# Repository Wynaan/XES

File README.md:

# XES

This repository details my end of degree project in Electronics Technology at Cegep Saint-Jean-sur-Richelieu.

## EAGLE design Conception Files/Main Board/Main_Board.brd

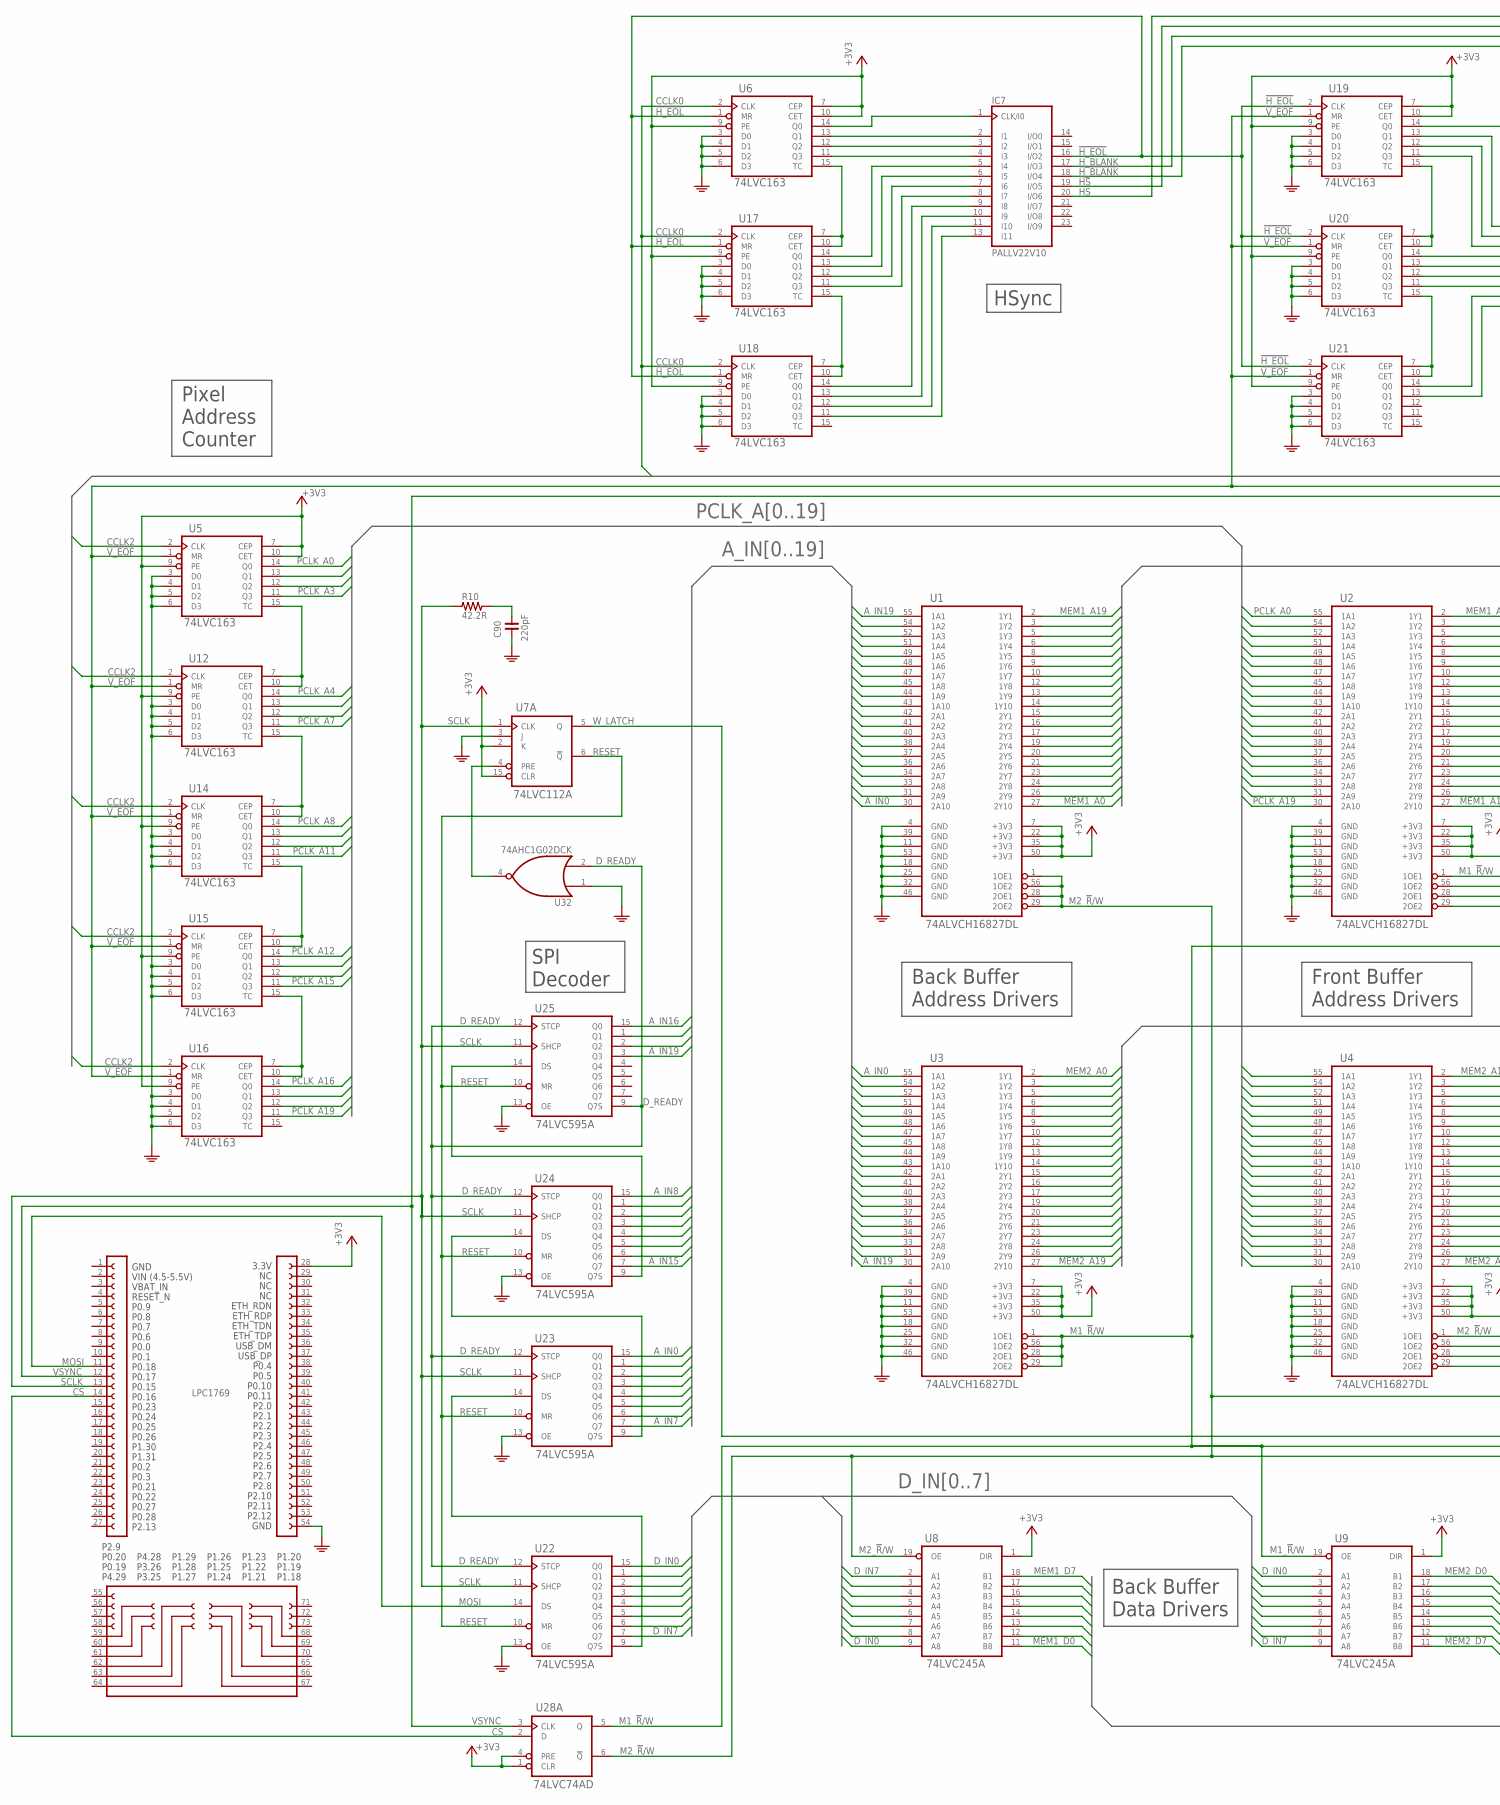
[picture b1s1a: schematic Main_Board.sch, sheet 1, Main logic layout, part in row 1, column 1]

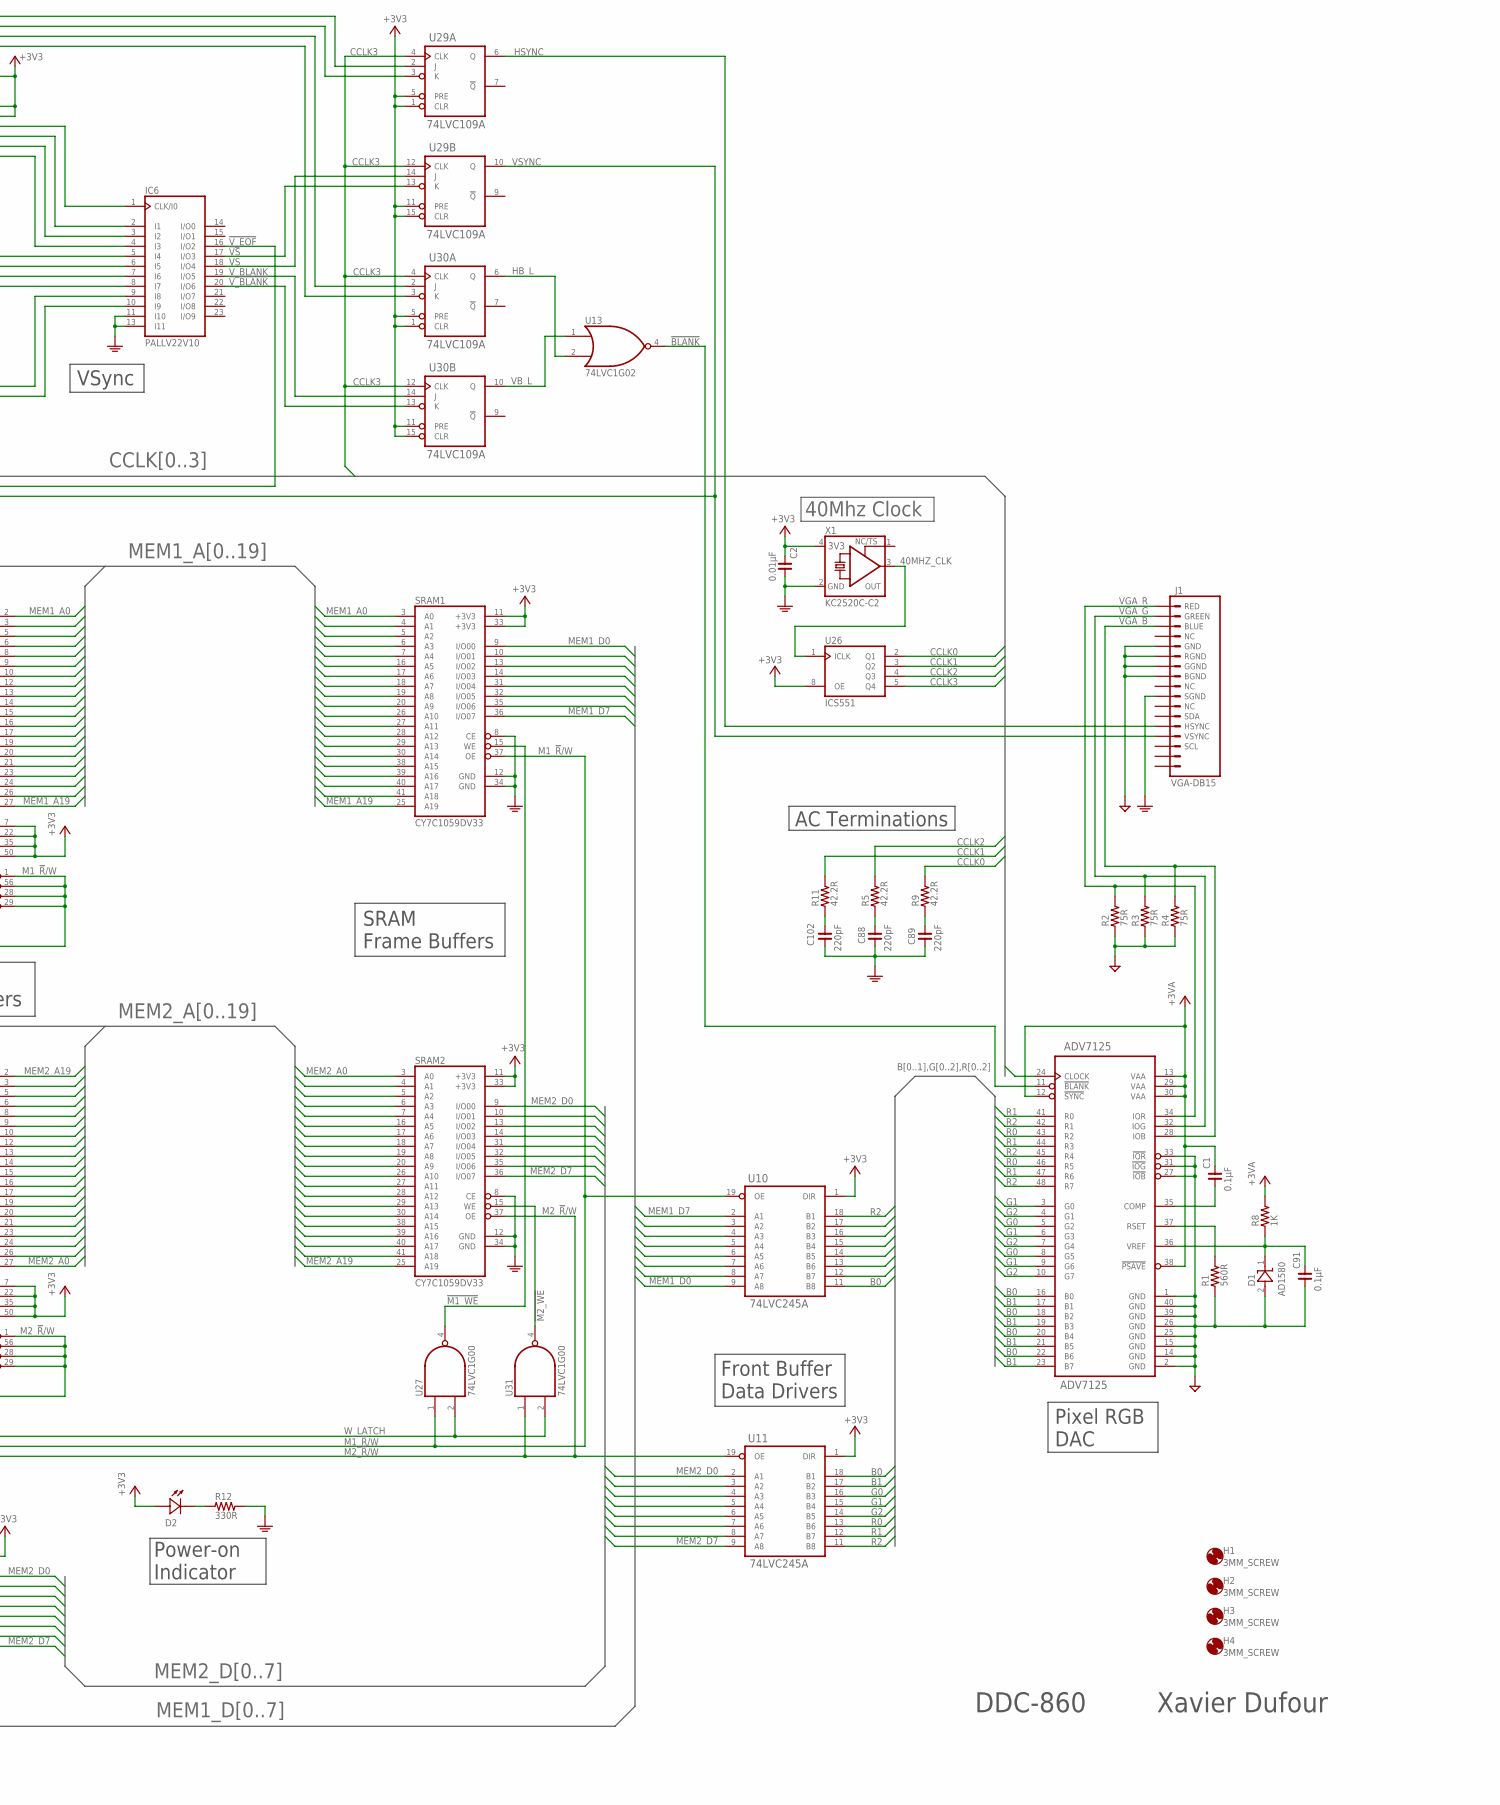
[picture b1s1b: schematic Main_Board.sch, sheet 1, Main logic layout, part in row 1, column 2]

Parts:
ADV7125: ADV7125; LQFP48(SOT313)
C1, C91: 0.1µF; C0603
C2: 0.01µF; C0603
C88, C89, C90, C102: 220pF; C0603
D1: AD1580; TO236-3(SOT23)
D2: DEL-1206; DEL1206
H1, H2, H3, H4: 3MM_SCREW; 3MM_HOLE
IC6, IC7: PALLV22V10; DIP24
J1: VGA-DB15; DB15-VGA-90DEG
LPC1769: LPCXPRESSO_LPC1769
R1: 560R; R0603
R2, R3, R4: 75R; R0603
R5, R9, R10, R11: 42.2R; R0603
R8: 1K; R0603
R12: 330R; R1206
SRAM1, SRAM2: CY7C1059DV33; TSOPII-44
U1, U2, U3, U4: 74ALVCH16827DL; SSOP56(SOT371)
U5, U6, U12, U14, U15, U16, U17, U18, U19, U20, U21: 74LVC163; SO16D(SOT109)
U7: 74LVC112A; SO16D(SOT109)
U8, U9, U10, U11: 74LVC245A; SO20DW(SOT163)
U13: 74LVC1G02; SC70-5(SOT353)
U22, U23, U24, U25: 74LVC595A; SO16D(SOT109)
U26: ICS551; SO08(SOT96)
U27, U31: 74LVC1G00; SC70-5(SOT353)
U28: 74LVC74AD; SO14(SOT108)
U29, U30: 74LVC109A; SO16D(SOT109)
U32: 74AHC1G02DCK; SC70-5(SOT353)
X1: KC2520C-C2; OSCXO2.5X2.0

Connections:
40MHZ_CLK: U26.1 (ICLK), X1.3 (OUT)
!BLANK: ADV7125.11 (!BLANK), U13.4 (Y)
!HS: IC7.19 (I/O5), U29.3 (K)
!H_BLANK: IC7.18 (I/O4), U30.3 (K)
!H_EOL: IC7.16 (I/O2), U6.1 (MR), U17.1 (MR), U18.1 (MR), U19.2 (CLK), U20.2 (CLK), U21.2 (CLK)
!M1_WE: SRAM1.15 (WE), U27.4 (Y)
!M2_WE: SRAM2.15 (WE), U31.4 (Y)
!VS: IC6.17 (I/O3), U29.13 (K)
!V_BLANK: IC6.20 (I/O6), U30.13 (K)
!V_EOF: IC6.16 (I/O2), U5.1 (MR), U12.1 (MR), U14.1 (MR), U15.1 (MR), U16.1 (MR), U19.1 (MR), U20.1 (MR), U21.1 (MR)
+3V3: C2.2, D2.A, IC6.24 (+3V3), IC7.24 (+3V3), LPC1769.28, SRAM1.11 (+3V3), SRAM1.33 (+3V3), SRAM2.11 (+3V3), SRAM2.33 (+3V3), U1.7 (+3V3), U1.22 (+3V3), U1.35 (+3V3), U1.50 (+3V3), U2.7 (+3V3), U2.22 (+3V3), U2.35 (+3V3), U2.50 (+3V3), U3.7 (+3V3), U3.22 (+3V3), U3.35 (+3V3), U3.50 (+3V3), U4.7 (+3V3), U4.22 (+3V3), U4.35 (+3V3), U4.50 (+3V3), U5.7 (CEP), U5.9 (PE), U5.10 (CET), U5.16 (+3V3), U6.7 (CEP), U6.9 (PE), U6.10 (CET), U6.16 (+3V3), U7.2 (K), U7.15 (CLR), U7.16 (+3V3), U8.1 (DIR), U8.20 (+3V3), U9.1 (DIR), U9.20 (+3V3), U10.1 (DIR), U10.20 (+3V3), U11.1 (DIR), U11.20 (+3V3), U12.9 (PE), U12.16 (+3V3), U13.5 (+3V3), U14.9 (PE), U14.16 (+3V3), U15.9 (PE), U15.16 (+3V3), U16.9 (PE), U16.16 (+3V3), U17.9 (PE), U17.16 (+3V3), U18.9 (PE), U18.16 (+3V3), U19.7 (CEP), U19.9 (PE), U19.10 (CET), U19.16 (+3V3), U20.9 (PE), U20.16 (+3V3), U21.9 (PE), U21.16 (+3V3), U22.16 (+3V3), U23.16 (+3V3), U24.16 (+3V3), U25.16 (+3V3), U26.7 (+3V3), U26.8 (OE), U27.5 (+3V3), U28.1 (CLR), U28.4 (PRE), U28.14 (+3V3), U29.1 (CLR), U29.5 (PRE), U29.11 (PRE), U29.15 (CLR), U29.16 (+3V3), U30.1 (CLR), U30.5 (PRE), U30.11 (PRE), U30.15 (CLR), U30.16 (+3V3), U31.5 (+3V3), U32.5 (+3V3), X1.4 (+3V3); also elsewhere on the board
+3VA: ADV7125.12 (!SYNC), ADV7125.13 (VAA), ADV7125.29 (VAA), ADV7125.30 (VAA), ADV7125.38 (!PSAVE), C1.2, R8.2; also elsewhere on the board
AGND: ADV7125.1 (GND), ADV7125.2 (GND), ADV7125.14 (GND), ADV7125.15 (GND), ADV7125.25 (GND), ADV7125.26 (GND), ADV7125.27 (!IOB), ADV7125.31 (!IOG), ADV7125.33 (!IOR), ADV7125.39 (GND), ADV7125.40 (GND), C91.1, D1.2 (V-), J1.5 (GND), J1.6 (RGND), J1.7 (GGND), J1.8 (BGND), R1.1, R2.1, R3.1, R4.1; also elsewhere on the board
A_IN0: U1.30 (2A10), U3.55 (1A1), U23.15 (Q0)
A_IN1: U1.31 (2A9), U3.54 (1A2), U23.1 (Q1)
A_IN2: U1.33 (2A8), U3.52 (1A3), U23.2 (Q2)
A_IN3: U1.34 (2A7), U3.51 (1A4), U23.3 (Q3)
A_IN4: U1.36 (2A6), U3.49 (1A5), U23.4 (Q4)
A_IN5: U1.37 (2A5), U3.48 (1A6), U23.5 (Q5)
A_IN6: U1.38 (2A4), U3.47 (1A7), U23.6 (Q6)
A_IN7: U1.40 (2A3), U3.45 (1A8), U23.7 (Q7)
A_IN8: U1.41 (2A2), U3.44 (1A9), U24.15 (Q0)
A_IN9: U1.42 (2A1), U3.43 (1A10), U24.1 (Q1)
A_IN10: U1.43 (1A10), U3.42 (2A1), U24.2 (Q2)
A_IN11: U1.44 (1A9), U3.41 (2A2), U24.3 (Q3)
A_IN12: U1.45 (1A8), U3.40 (2A3), U24.4 (Q4)
A_IN13: U1.47 (1A7), U3.38 (2A4), U24.5 (Q5)
A_IN14: U1.48 (1A6), U3.37 (2A5), U24.6 (Q6)
A_IN15: U1.49 (1A5), U3.36 (2A6), U24.7 (Q7)
A_IN16: U1.51 (1A4), U3.34 (2A7), U25.15 (Q0)
A_IN17: U1.52 (1A3), U3.33 (2A8), U25.1 (Q1)
A_IN18: U1.54 (1A2), U3.31 (2A9), U25.2 (Q2)
A_IN19: U1.55 (1A1), U3.30 (2A10), U25.3 (Q3)
B0: ADV7125.16 (B0), ADV7125.18 (B2), ADV7125.20 (B4), ADV7125.22 (B6), U10.11 (B8), U11.18 (B1)
B1: ADV7125.17 (B1), ADV7125.19 (B3), ADV7125.21 (B5), ADV7125.23 (B7), U10.12 (B7), U11.17 (B2)
CCLK0: R9.2, U6.2 (CLK), U17.2 (CLK), U18.2 (CLK), U26.2 (Q1)
CCLK1: ADV7125.24 (CLOCK), R11.2, U26.3 (Q2)
CCLK2: R5.2, U5.2 (CLK), U12.2 (CLK), U14.2 (CLK), U15.2 (CLK), U16.2 (CLK), U26.4 (Q3)
CCLK3: U26.5 (Q4), U29.4 (CLK), U29.12 (CLK), U30.4 (CLK), U30.12 (CLK)
COMP: ADV7125.35 (COMP), C1.1
CS: LPC1769.14, U28.2 (D)
D_IN0: U8.9 (A8), U9.2 (A1), U22.15 (Q0)
D_IN1: U8.8 (A7), U9.3 (A2), U22.1 (Q1)
D_IN2: U8.7 (A6), U9.4 (A3), U22.2 (Q2)
D_IN3: U8.6 (A5), U9.5 (A4), U22.3 (Q3)
D_IN4: U8.5 (A4), U9.6 (A5), U22.4 (Q4)
D_IN5: U8.4 (A3), U9.7 (A6), U22.5 (Q5)
D_IN6: U8.3 (A2), U9.8 (A7), U22.6 (Q6)
D_IN7: U8.2 (A1), U9.9 (A8), U22.7 (Q7)
D_READY: U22.12 (STCP), U23.12 (STCP), U24.12 (STCP), U25.9 (Q7S), U25.12 (STCP), U32.2 (B)
G0: ADV7125.5 (G2), ADV7125.8 (G5), U10.13 (B6), U11.16 (B3)
G1: ADV7125.3 (G0), ADV7125.6 (G3), ADV7125.9 (G6), U10.14 (B5), U11.15 (B4)
G2: ADV7125.4 (G1), ADV7125.7 (G4), ADV7125.10 (G7), U10.15 (B4), U11.14 (B5)
GND: C2.1, C88.1, C89.1, C90.1, C102.1, IC6.11 (I10), IC6.12 (GND), IC6.13 (I11), IC7.12 (GND), J1.10 (SGND), LPC1769.54, R12.2, SRAM1.8 (CE), SRAM1.12 (GND), SRAM1.34 (GND), SRAM2.8 (CE), SRAM2.12 (GND), SRAM2.34 (GND), U1.4 (GND), U1.11 (GND), U1.18 (GND), U1.25 (GND), U1.32 (GND), U1.39 (GND), U1.46 (GND), U1.53 (GND), U2.4 (GND), U2.11 (GND), U2.18 (GND), U2.25 (GND), U2.32 (GND), U2.39 (GND), U2.46 (GND), U2.53 (GND), U3.4 (GND), U3.11 (GND), U3.18 (GND), U3.25 (GND), U3.32 (GND), U3.39 (GND), U3.46 (GND), U3.53 (GND), U4.4 (GND), U4.11 (GND), U4.18 (GND), U4.25 (GND), U4.32 (GND), U4.39 (GND), U4.46 (GND), U4.53 (GND), U5.3 (D0), U5.4 (D1), U5.5 (D2), U5.6 (D3), U5.8 (GND), U6.3 (D0), U6.4 (D1), U6.5 (D2), U6.6 (D3), U6.8 (GND), U7.3 (J), U7.8 (GND), U8.10 (GND), U9.10 (GND), U10.10 (GND), U11.10 (GND), U12.3 (D0), U12.4 (D1), U12.5 (D2), U12.6 (D3), U12.8 (GND), U13.3 (GND), U14.3 (D0), U14.4 (D1), U14.5 (D2), U14.6 (D3), U14.8 (GND), U15.3 (D0), U15.4 (D1), U15.5 (D2), U15.6 (D3), U15.8 (GND), U16.3 (D0), U16.4 (D1), U16.5 (D2), U16.6 (D3), U16.8 (GND), U17.3 (D0), U17.4 (D1), U17.5 (D2), U17.6 (D3), U17.8 (GND), U18.3 (D0), U18.4 (D1), U18.5 (D2), U18.6 (D3), U18.8 (GND), U19.3 (D0), U19.4 (D1), U19.5 (D2), U19.6 (D3), U19.8 (GND), U20.3 (D0), U20.4 (D1), U20.5 (D2), U20.6 (D3), U20.8 (GND), U21.3 (D0), U21.4 (D1), U21.5 (D2), U21.6 (D3), U21.8 (GND), U22.8 (GND), U22.13 (OE), U23.8 (GND), U23.13 (OE), U24.8 (GND), U24.13 (OE), U25.8 (GND), U25.13 (OE), U26.6 (GND), U27.3 (GND), U28.7 (GND), U29.8 (GND), U30.8 (GND), U31.3 (GND), U32.1 (A), U32.3 (GND), X1.2 (GND); also elsewhere on the board
HB_L: U13.2 (B), U30.6 (Q)
HS: IC7.20 (I/O6), U29.2 (J)
HSYNC: J1.13 (HSYNC), U29.6 (Q)
H_BLANK: IC7.17 (I/O3), U30.2 (J)
H_Q0: IC7.1 (CLK/I0), U6.14 (Q0)
H_Q1: IC7.2 (I1), U6.13 (Q1)
H_Q2: IC7.3 (I2), U6.12 (Q2)
H_Q3: IC7.4 (I3), U6.11 (Q3)
H_Q4: IC7.5 (I4), U17.14 (Q0)
H_Q5: IC7.6 (I5), U17.13 (Q1)
H_Q6: IC7.7 (I6), U17.12 (Q2)
H_Q7: IC7.8 (I7), U17.11 (Q3)
H_Q8: IC7.9 (I8), U18.14 (Q0)
H_Q9: IC7.10 (I9), U18.13 (Q1)
H_Q10: IC7.11 (I10), U18.12 (Q2)
H_Q11: IC7.13 (I11), U18.11 (Q3)
M1_!R!/W: SRAM1.37 (OE), U2.1 (1OE1), U2.28 (2OE1), U2.29 (2OE2), U2.56 (1OE2), U3.1 (1OE1), U3.28 (2OE1), U3.29 (2OE2), U3.56 (1OE2), U9.19 (OE), U10.19 (OE), U27.1 (B), U28.5 (Q)
M2_!R!/W: SRAM2.37 (OE), U1.1 (1OE1), U1.28 (2OE1), U1.29 (2OE2), U1.56 (1OE2), U4.1 (1OE1), U4.28 (2OE1), U4.29 (2OE2), U4.56 (1OE2), U8.19 (OE), U11.19 (OE), U28.6 (!Q), U31.1 (B)
MEM1_A0: SRAM1.3 (A0), U1.27 (2Y10), U2.2 (1Y1)
MEM1_A1: SRAM1.4 (A1), U1.26 (2Y9), U2.3 (1Y2)
MEM1_A2: SRAM1.5 (A2), U1.24 (2Y8), U2.5 (1Y3)
MEM1_A3: SRAM1.6 (A3), U1.23 (2Y7), U2.6 (1Y4)
MEM1_A4: SRAM1.7 (A4), U1.21 (2Y6), U2.8 (1Y5)
MEM1_A5: SRAM1.16 (A5), U1.20 (2Y5), U2.9 (1Y6)
MEM1_A6: SRAM1.17 (A6), U1.19 (2Y4), U2.10 (1Y7)
MEM1_A7: SRAM1.18 (A7), U1.17 (2Y3), U2.12 (1Y8)
MEM1_A8: SRAM1.19 (A8), U1.16 (2Y2), U2.13 (1Y9)
MEM1_A9: SRAM1.20 (A9), U1.15 (2Y1), U2.14 (1Y10)
MEM1_A10: SRAM1.26 (A10), U1.14 (1Y10), U2.15 (2Y1)
MEM1_A11: SRAM1.27 (A11), U1.13 (1Y9), U2.16 (2Y2)
MEM1_A12: SRAM1.28 (A12), U1.12 (1Y8), U2.17 (2Y3)
MEM1_A13: SRAM1.29 (A13), U1.10 (1Y7), U2.19 (2Y4)
MEM1_A14: SRAM1.30 (A14), U1.9 (1Y6), U2.20 (2Y5)
MEM1_A15: SRAM1.38 (A15), U1.8 (1Y5), U2.21 (2Y6)
MEM1_A16: SRAM1.39 (A16), U1.6 (1Y4), U2.23 (2Y7)
MEM1_A17: SRAM1.40 (A17), U1.5 (1Y3), U2.24 (2Y8)
MEM1_A18: SRAM1.41 (A18), U1.3 (1Y2), U2.26 (2Y9)
MEM1_A19: SRAM1.25 (A19), U1.2 (1Y1), U2.27 (2Y10)
MEM1_D0: SRAM1.9 (I/O00), U8.11 (B8), U10.9 (A8)
MEM1_D1: SRAM1.10 (I/O01), U8.12 (B7), U10.8 (A7)
MEM1_D2: SRAM1.13 (I/O02), U8.13 (B6), U10.7 (A6)
MEM1_D3: SRAM1.14 (I/O03), U8.14 (B5), U10.6 (A5)
MEM1_D4: SRAM1.31 (I/O04), U8.15 (B4), U10.5 (A4)
MEM1_D5: SRAM1.32 (I/O05), U8.16 (B3), U10.4 (A3)
MEM1_D6: SRAM1.35 (I/O06), U8.17 (B2), U10.3 (A2)
MEM1_D7: SRAM1.36 (I/O07), U8.18 (B1), U10.2 (A1)
MEM2_A0: SRAM2.3 (A0), U3.2 (1Y1), U4.27 (2Y10)
MEM2_A1: SRAM2.4 (A1), U3.3 (1Y2), U4.26 (2Y9)
MEM2_A2: SRAM2.5 (A2), U3.5 (1Y3), U4.24 (2Y8)
MEM2_A3: SRAM2.6 (A3), U3.6 (1Y4), U4.23 (2Y7)
MEM2_A4: SRAM2.7 (A4), U3.8 (1Y5), U4.21 (2Y6)
MEM2_A5: SRAM2.16 (A5), U3.9 (1Y6), U4.20 (2Y5)
MEM2_A6: SRAM2.17 (A6), U3.10 (1Y7), U4.19 (2Y4)
MEM2_A7: SRAM2.18 (A7), U3.12 (1Y8), U4.17 (2Y3)
MEM2_A8: SRAM2.19 (A8), U3.13 (1Y9), U4.16 (2Y2)
MEM2_A9: SRAM2.20 (A9), U3.14 (1Y10), U4.15 (2Y1)
MEM2_A10: SRAM2.26 (A10), U3.15 (2Y1), U4.14 (1Y10)
MEM2_A11: SRAM2.27 (A11), U3.16 (2Y2), U4.13 (1Y9)
MEM2_A12: SRAM2.28 (A12), U3.17 (2Y3), U4.12 (1Y8)
MEM2_A13: SRAM2.29 (A13), U3.19 (2Y4), U4.10 (1Y7)
MEM2_A14: SRAM2.30 (A14), U3.20 (2Y5), U4.9 (1Y6)
MEM2_A15: SRAM2.38 (A15), U3.21 (2Y6), U4.8 (1Y5)
MEM2_A16: SRAM2.39 (A16), U3.23 (2Y7), U4.6 (1Y4)
MEM2_A17: SRAM2.40 (A17), U3.24 (2Y8), U4.5 (1Y3)
MEM2_A18: SRAM2.41 (A18), U3.26 (2Y9), U4.3 (1Y2)
MEM2_A19: SRAM2.25 (A19), U3.27 (2Y10), U4.2 (1Y1)
MEM2_D0: SRAM2.9 (I/O00), U9.18 (B1), U11.2 (A1)
MEM2_D1: SRAM2.10 (I/O01), U9.17 (B2), U11.3 (A2)
MEM2_D2: SRAM2.13 (I/O02), U9.16 (B3), U11.4 (A3)
MEM2_D3: SRAM2.14 (I/O03), U9.15 (B4), U11.5 (A4)
MEM2_D4: SRAM2.31 (I/O04), U9.14 (B5), U11.6 (A5)
MEM2_D5: SRAM2.32 (I/O05), U9.13 (B6), U11.7 (A6)
MEM2_D6: SRAM2.35 (I/O06), U9.12 (B7), U11.8 (A7)
MEM2_D7: SRAM2.36 (I/O07), U9.11 (B8), U11.9 (A8)
MOSI: LPC1769.11, U22.14 (DS)
unnamed: U15.15 (TC), U16.7 (CEP), U16.10 (CET)
unnamed: C88.2, R5.1
unnamed: U22.9 (Q7S), U23.14 (DS)
unnamed: U7.4 (PRE), U32.4 (Y)
unnamed: C89.2, R9.1
unnamed: U23.9 (Q7S), U24.14 (DS)
unnamed: U24.9 (Q7S), U25.14 (DS)
unnamed: U5.15 (TC), U12.7 (CEP), U12.10 (CET)
unnamed: U12.15 (TC), U14.7 (CEP), U14.10 (CET)
unnamed: U14.15 (TC), U15.7 (CEP), U15.10 (CET)
unnamed: C90.2, R10.2
unnamed: U6.15 (TC), U17.7 (CEP), U17.10 (CET)
unnamed: U17.15 (TC), U18.7 (CEP), U18.10 (CET)
unnamed: D2.C, R12.1
unnamed: C102.2, R11.1
unnamed: U19.15 (TC), U20.7 (CEP), U20.10 (CET)
unnamed: U20.15 (TC), U21.7 (CEP), U21.10 (CET)
PCLK_A0: U2.55 (1A1), U4.30 (2A10), U5.14 (Q0)
PCLK_A1: U2.54 (1A2), U4.31 (2A9), U5.13 (Q1)
PCLK_A2: U2.52 (1A3), U4.33 (2A8), U5.12 (Q2)
PCLK_A3: U2.51 (1A4), U4.34 (2A7), U5.11 (Q3)
PCLK_A4: U2.49 (1A5), U4.36 (2A6), U12.14 (Q0)
PCLK_A5: U2.48 (1A6), U4.37 (2A5), U12.13 (Q1)
PCLK_A6: U2.47 (1A7), U4.38 (2A4), U12.12 (Q2)
PCLK_A7: U2.45 (1A8), U4.40 (2A3), U12.11 (Q3)
PCLK_A8: U2.44 (1A9), U4.41 (2A2), U14.14 (Q0)
PCLK_A9: U2.43 (1A10), U4.42 (2A1), U14.13 (Q1)
PCLK_A10: U2.42 (2A1), U4.43 (1A10), U14.12 (Q2)
PCLK_A11: U2.41 (2A2), U4.44 (1A9), U14.11 (Q3)
PCLK_A12: U2.40 (2A3), U4.45 (1A8), U15.14 (Q0)
PCLK_A13: U2.38 (2A4), U4.47 (1A7), U15.13 (Q1)
PCLK_A14: U2.37 (2A5), U4.48 (1A6), U15.12 (Q2)
PCLK_A15: U2.36 (2A6), U4.49 (1A5), U15.11 (Q3)
PCLK_A16: U2.34 (2A7), U4.51 (1A4), U16.14 (Q0)
PCLK_A17: U2.33 (2A8), U4.52 (1A3), U16.13 (Q1)
PCLK_A18: U2.31 (2A9), U4.54 (1A2), U16.12 (Q2)
PCLK_A19: U2.30 (2A10), U4.55 (1A1), U16.11 (Q3)
R0: ADV7125.43 (R2), ADV7125.46 (R5), U10.16 (B3), U11.13 (B6)
R1: ADV7125.41 (R0), ADV7125.44 (R3), ADV7125.47 (R6), U10.17 (B2), U11.12 (B7)
R2: ADV7125.42 (R1), ADV7125.45 (R4), ADV7125.48 (R7), U10.18 (B1), U11.11 (B8)
RESET: U7.6 (!Q), U22.10 (MR), U23.10 (MR), U24.10 (MR), U25.10 (MR)
RSET: ADV7125.37 (RSET), R1.2
SCLK: LPC1769.13, R10.1, U7.1 (CLK), U22.11 (SHCP), U23.11 (SHCP), U24.11 (SHCP), U25.11 (SHCP)
VB_L: U13.1 (A), U30.10 (Q)
VGA_B: ADV7125.28 (IOB), J1.3 (BLUE), R4.2
VGA_G: ADV7125.32 (IOG), J1.2 (GREEN), R3.2
VGA_R: ADV7125.34 (IOR), J1.1 (RED), R2.2
VREF: ADV7125.36 (VREF), C91.2, D1.1 (V+), R8.1
VS: IC6.18 (I/O4), U29.14 (J)
VSYNC: J1.14 (VSYNC), LPC1769.12, U28.3 (CLK), U29.10 (Q)
V_BLANK: IC6.19 (I/O5), U30.14 (J)
V_Q0: IC6.1 (CLK/I0), U19.14 (Q0)
V_Q1: IC6.2 (I1), U19.13 (Q1)
V_Q2: IC6.3 (I2), U19.12 (Q2)
V_Q3: IC6.4 (I3), U19.11 (Q3)
V_Q4: IC6.5 (I4), U20.14 (Q0)
V_Q5: IC6.6 (I5), U20.13 (Q1)
V_Q6: IC6.7 (I6), U20.12 (Q2)
V_Q7: IC6.8 (I7), U20.11 (Q3)
V_Q8: IC6.9 (I8), U21.14 (Q0)
V_Q9: IC6.10 (I9), U21.13 (Q1)
W_LATCH: U7.5 (Q), U27.2 (A), U31.2 (A)

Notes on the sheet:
SRAM Frame Buffers
Back Buffer Address Drivers
Front Buffer Address Drivers
Front Buffer Data Drivers
Back Buffer Data Drivers
Pixel Address Counter
SPI Decoder
Pixel RGB DAC
VSync
HSync
40Mhz Clock
DDC-860 Xavier Dufour
Power-on Indicator
AC Terminations

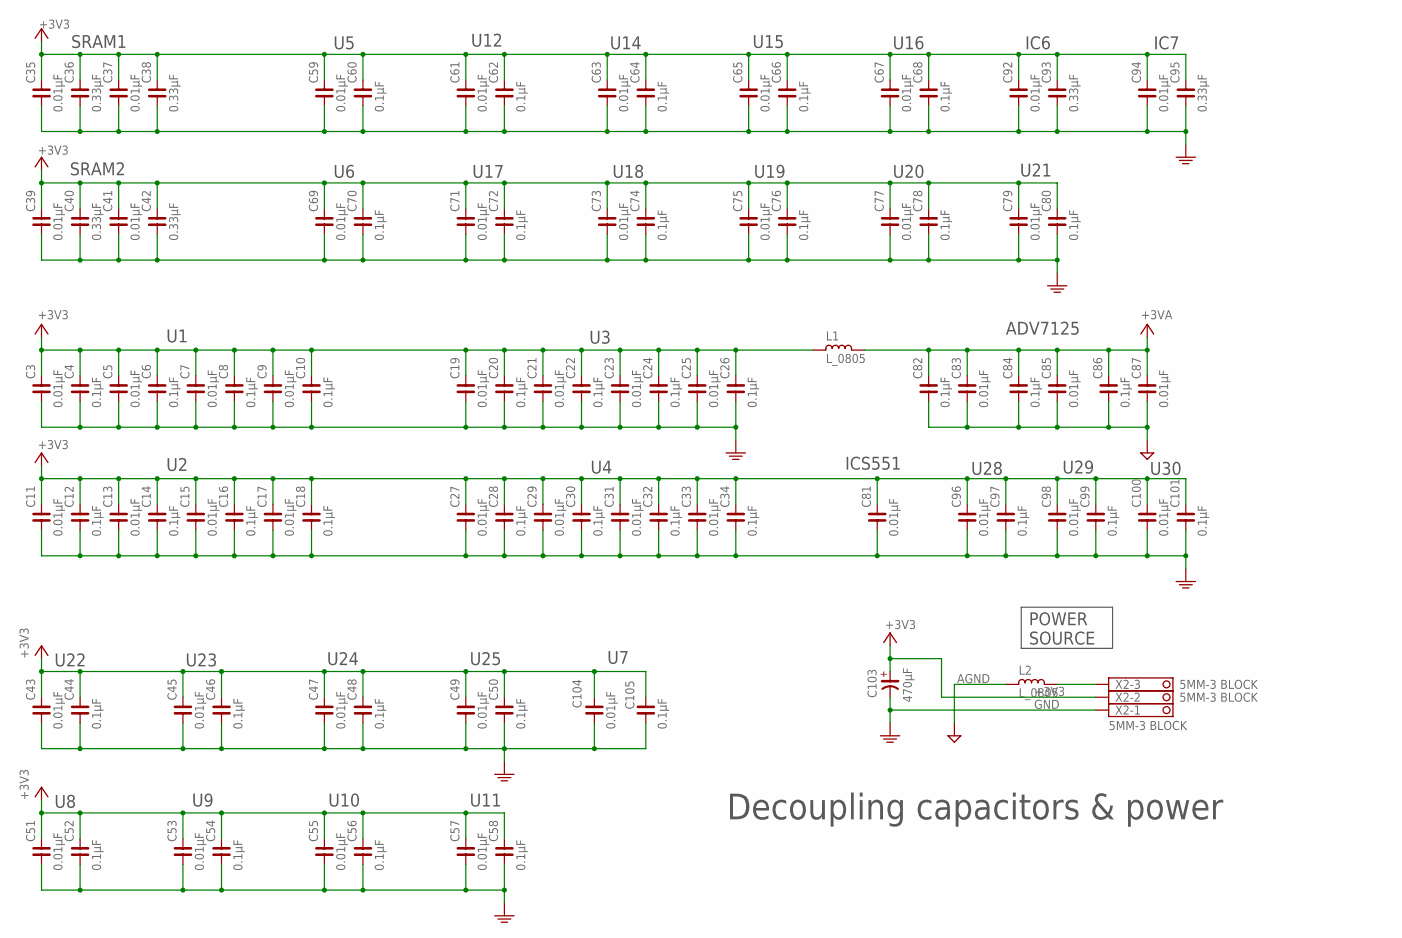
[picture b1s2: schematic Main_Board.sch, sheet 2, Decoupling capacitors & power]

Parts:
C3, C5, C7, C9, C11, C13, C15, C17, C19, C21, C23, C25, C27, C29, C31, C33, C35, C37, C39, C41, C43, C45, C47, C49, C51, C53, C55, C57, C59, C61, C63, C65, C67, C69, C71, C73, C75, C77, C79, C81, C83, C85, C87, C92, C94, C96, C98, C100, C104: 0.01µF; C0603
C4, C6, C8, C10, C12, C14, C16, C18, C20, C22, C24, C26, C28, C30, C32, C34, C44, C46, C48, C50, C52, C54, C56, C58, C60, C62, C64, C66, C68, C70, C72, C74, C76, C78, C80, C82, C84, C86, C97, C99, C101, C105: 0.1µF; C0603
C36, C38, C40, C42, C93, C95: 0.33µF; C0603
C103: 470µF; CSV-G
L1, L2: L_0805; L0805
X2: 5MM-3 BLOCK; TERMINAL-BLOCK-3-PIN-5MM

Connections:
+3V3: C3.2, C4.2, C5.2, C6.2, C7.2, C8.2, C9.2, C10.2, C11.2, C12.2, C13.2, C14.2, C15.2, C16.2, C17.2, C18.2, C19.2, C20.2, C21.2, C22.2, C23.2, C24.2, C25.2, C26.2, C27.2, C28.2, C29.2, C30.2, C31.2, C32.2, C33.2, C34.2, C35.2, C36.2, C37.2, C38.2, C39.2, C40.2, C41.2, C42.2, C43.2, C44.2, C45.2, C46.2, C47.2, C48.2, C49.2, C50.2, C51.2, C52.2, C53.2, C54.2, C55.2, C56.2, C57.2, C58.2, C59.2, C60.2, C61.2, C62.2, C63.2, C64.2, C65.2, C66.2, C67.2, C68.2, C69.2, C70.2, C71.2, C72.2, C73.2, C74.2, C75.2, C76.2, C77.2, C78.2, C79.2, C80.2, C81.2, C92.2, C93.2, C94.2, C95.2, C96.2, C97.2, C98.2, C99.2, C100.2, C101.2, C103.+, C104.2, C105.2, L1.2, X2.2; also elsewhere on the board
+3VA: C82.2, C83.2, C84.2, C85.2, C86.2, C87.2, L1.1; also elsewhere on the board
AGND: C82.1, C83.1, C84.1, C85.1, C86.1, C87.1, L2.2; also elsewhere on the board
GND: C3.1, C4.1, C5.1, C6.1, C7.1, C8.1, C9.1, C10.1, C11.1, C12.1, C13.1, C14.1, C15.1, C16.1, C17.1, C18.1, C19.1, C20.1, C21.1, C22.1, C23.1, C24.1, C25.1, C26.1, C27.1, C28.1, C29.1, C30.1, C31.1, C32.1, C33.1, C34.1, C35.1, C36.1, C37.1, C38.1, C39.1, C40.1, C41.1, C42.1, C43.1, C44.1, C45.1, C46.1, C47.1, C48.1, C49.1, C50.1, C51.1, C52.1, C53.1, C54.1, C55.1, C56.1, C57.1, C58.1, C59.1, C60.1, C61.1, C62.1, C63.1, C64.1, C65.1, C66.1, C67.1, C68.1, C69.1, C70.1, C71.1, C72.1, C73.1, C74.1, C75.1, C76.1, C77.1, C78.1, C79.1, C80.1, C81.1, C92.1, C93.1, C94.1, C95.1, C96.1, C97.1, C98.1, C99.1, C100.1, C101.1, C103.-, C104.1, C105.1, X2.1; also elsewhere on the board
SUPPLY_REF: L2.1, X2.3

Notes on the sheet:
Decoupling capacitors & power
U10
U11
SRAM1
SRAM2
U22
U23
U24
U25
U12
U14
U15
U16
U17
U18
U19
U20
U21
ICS551
ADV7125
U28
U29
U30
IC6
IC7
POWER SOURCE

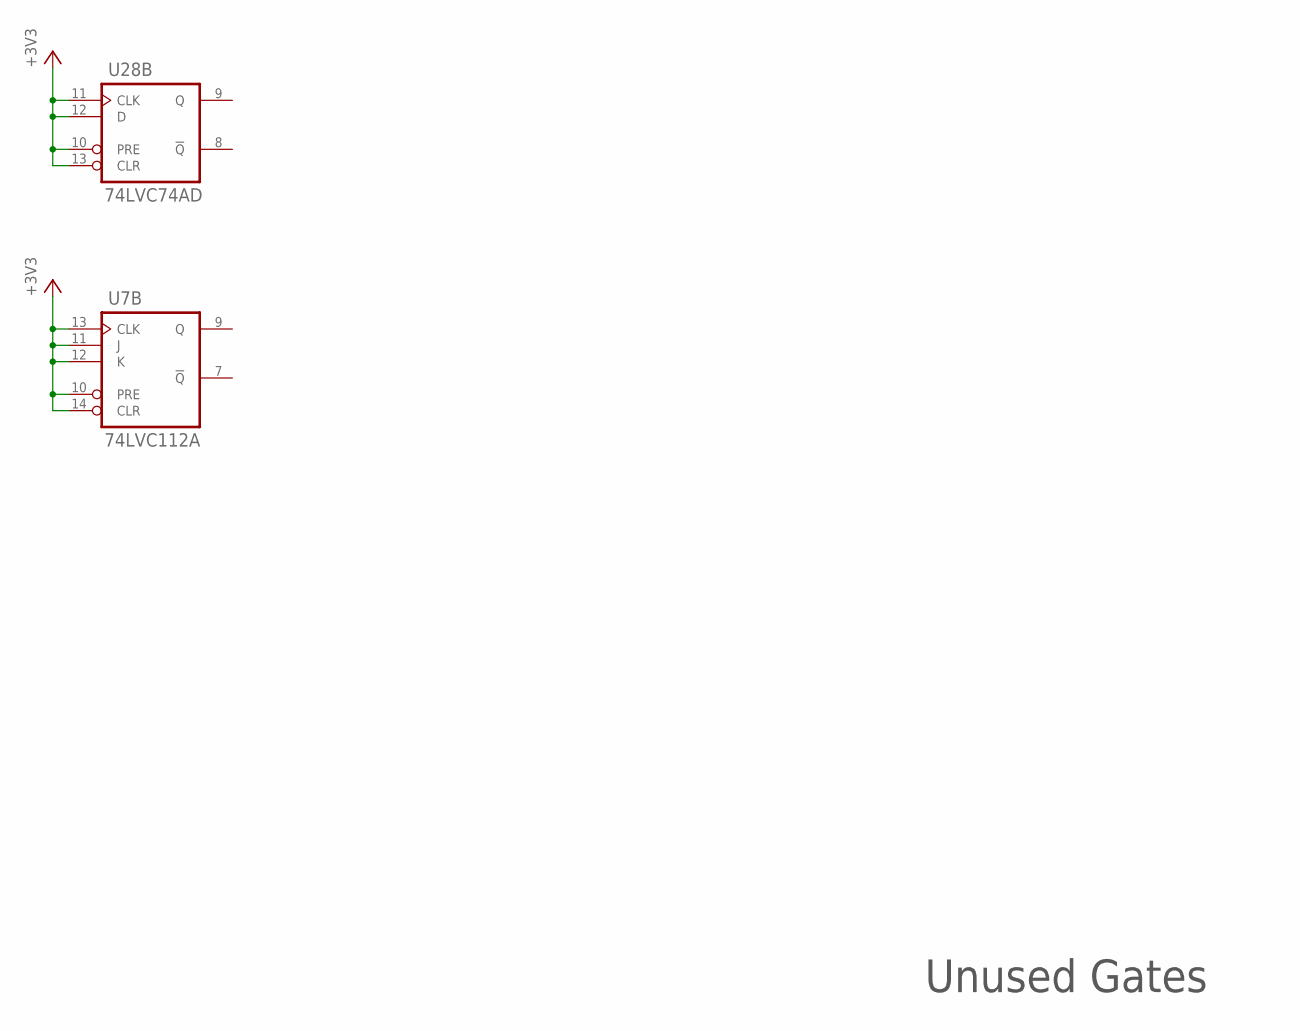
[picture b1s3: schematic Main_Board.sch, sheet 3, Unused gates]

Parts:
U7: 74LVC112A; SO16D(SOT109)
U28: 74LVC74AD; SO14(SOT108)

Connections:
+3V3: U7.10 (PRE), U7.11 (J), U7.12 (K), U7.13 (CLK), U7.14 (CLR), U7.16 (+3V3), U28.10 (PRE), U28.11 (CLK), U28.12 (D), U28.13 (CLR), U28.14 (+3V3); also elsewhere on the board
GND: U7.8 (GND), U28.7 (GND); also elsewhere on the board

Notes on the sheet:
Unused Gates

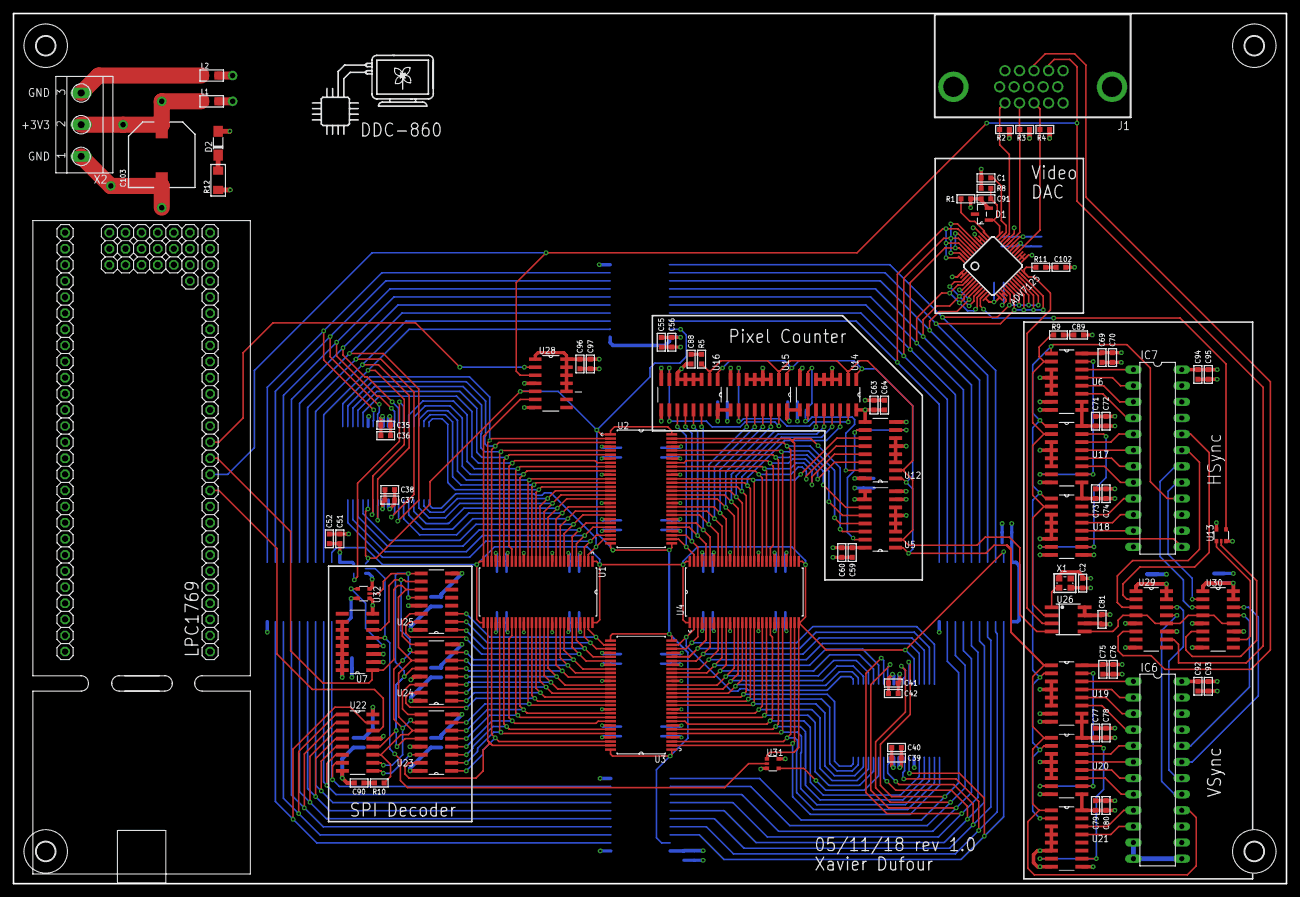
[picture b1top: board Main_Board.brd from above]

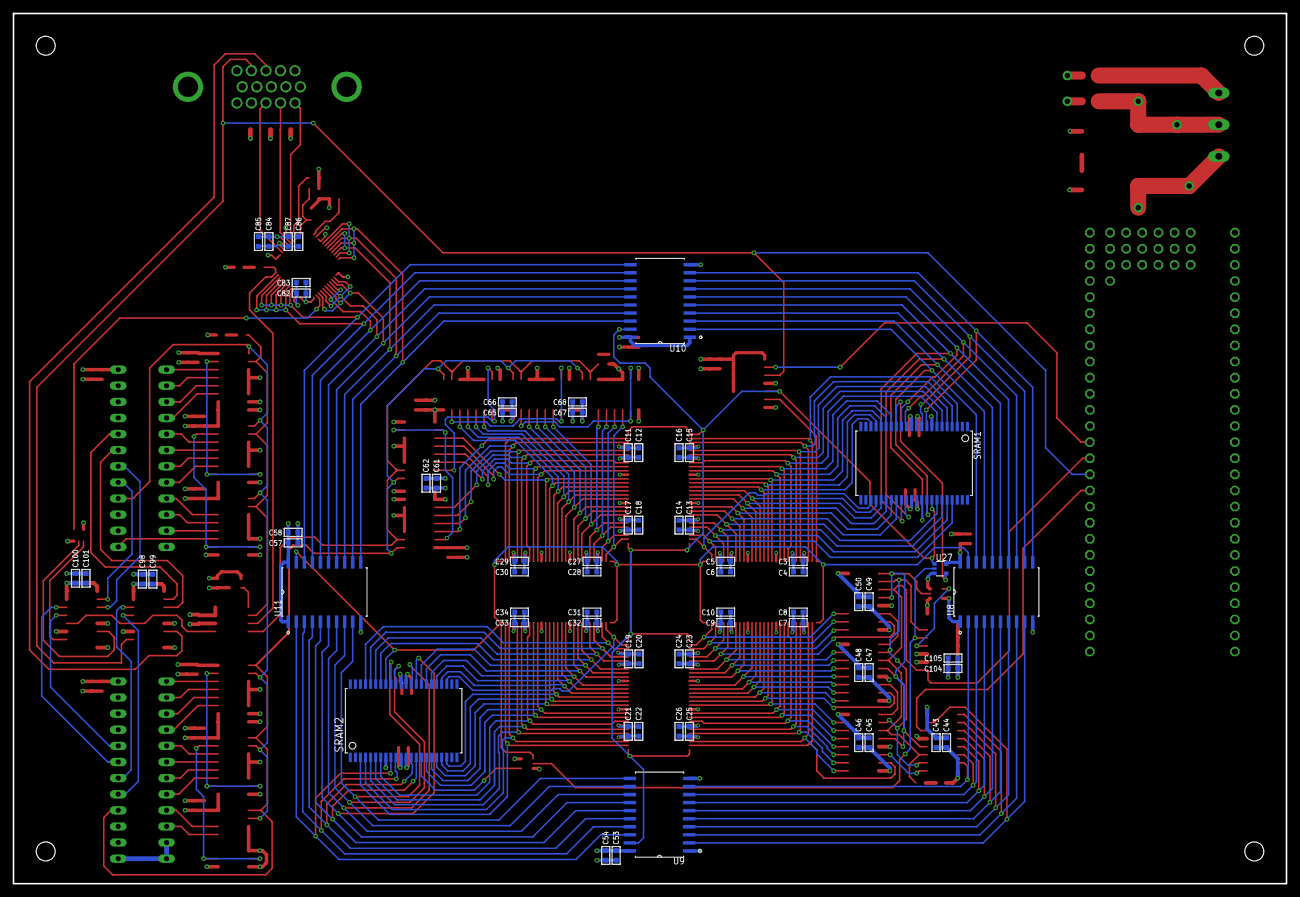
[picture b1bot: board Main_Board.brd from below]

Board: 4 copper layers, 200.7 x 137.2 mm, 164 parts (69 on the bottom side), 192 nets.

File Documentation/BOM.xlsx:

Qty | Value | Device | Package | Parts | Description
50 | 0.01µF | GCM188R72A103KA37J | C0603 | C2, C3, C5, C7, C9, C11, C13, C15, C17, C19, C21, C23, C25, C27, C29, C31, C33,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 | SMD Ceramic non-polarized capacitor
44 | 0.1µF | CC0603KRX7R7BB104 | C0603 | C1, C4, C6, C8, C10, C12, C14, C16, C18, C20, C22, C24, C26, C28, C30, C32, C34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 | SMD Ceramic non-polarized capacitor
11 |  | 74LVC163D | SO16(SOT109) | U5, U6, U12, U14, U15, U16, U17, U18, U19, U20, U21 | 4-bit synchronous counter with RCO output
6 | 0.33µF | GRM188R71C334KA01D | C0603 | C36, C38, C40, C42, C93, C95 | SMD Non-polarized capacitor
4 | 42.2R | RP73PF1J42R2BTDF | R0603 | R5, R9, R10, R11 | SMD Resistor 0.1%
4 |  | 74ALVCH16827DL | SSOP56(SOT371) | U1, U2, U3, U4 | 20-bit buffer/driver with 3-state outputs
4 |  | 74LVC245AD | SO20W(SOT163) | U8, U9, U10, U11 | Octal bus transceiver with 3-state outputs
4 |  | 74LVC595AD | SO16(SOT109) | U22, U23, U24, U25 | 8-bit serial-in/serial-out or parallel-out shift register with 3-state ouput
3 | 220pF | C0603C221K2RACTU | C0603 | C88, C89, C90, C102 | SMD Ceramic non-polarized capacitor
3 | 75R | RNCP0603FTD75R0 | R0603 | R2, R3, R4 | SMD Resistor 1%
2 |  | 74LVC109A | SO16(SOT109) | U29, U30 | Dual JK Latch, positive edge triggered
2 |  | 74LVC1G00GW | SC70-5(SOT353) | U27, U31 | Single NOR gate
2 |  | CY7C1059DV33-10ZSXI | TSOPII-44 | SRAM1, SRAM2 | 1M x 8bit Asynchronous SRAM
2 |  | 742792097 | L0805 | L1, L2 | Ferrite bead 1.5KOhm
1 | 330R | CRCW0805330RFKEAC | R1206 | R12 | SMD Resistor 1%
1 |  | QBLP615-IG | D1206 | D2 | Light Emitting Diode
1 | 1K | RR0816P-102-D | R0603 | R8 | SMD Resistor
1 | 470µF | UWT1E471MNL1GS | Radial 10mm SMD | C103 | SMD Electrolytic polarized capacitor
1 | 560R | AC0603FR-07560RL | R0603 | R1 | SMD Resistor
1 |  | 74AHC1G02DCKR | SC70-5(SOT353) | IC5 | Single NOR gate
1 |  | 74LVC112AD | SO16(SOT109) | U7 | Dual JK Latch, negative edge triggered
1 |  | 74LVC1G02DCKR | SC70-5(SOT353) | U13 | Single NOR gate
1 |  | 74LVC74AD | SO14(SOT108) | U28 | Dual D Latch, positive edge triggered
1 |  | AD1580BRTZ | SOT23 | D1 | 1.2 V Micropower, Precision 1.2 V Micropower, Precision
1 |  | ADV7125JSTZ330 | LQFP48 | ADV7125 | triple 8-bit 3.3V high speed video DAC, 330MHz grade
1 |  | ICS551 | SO8(SOT96) | U26 | Clock fanout buffer 1 to 4, 160MHz with 3-state outputs
1 |  | KC2520C40.0000C2YE00 | 2.5X2.0_KXO-V95 | X1 | SMD crystal oscillator
1 |  | LS25-3.3 | LS25-3.3 |  | Power supply 120VAC to 3.3VDC, 6A
1 |  | SCREW_BLOCK | SCREW_BLOCK5-3PIN | J2 | Screw terminal block 5mm spacing 3-pins
1 |  | 9561525613 | DB15-VGA-90DEG | J1 | DB-15 connector for VGA, 90 degrees

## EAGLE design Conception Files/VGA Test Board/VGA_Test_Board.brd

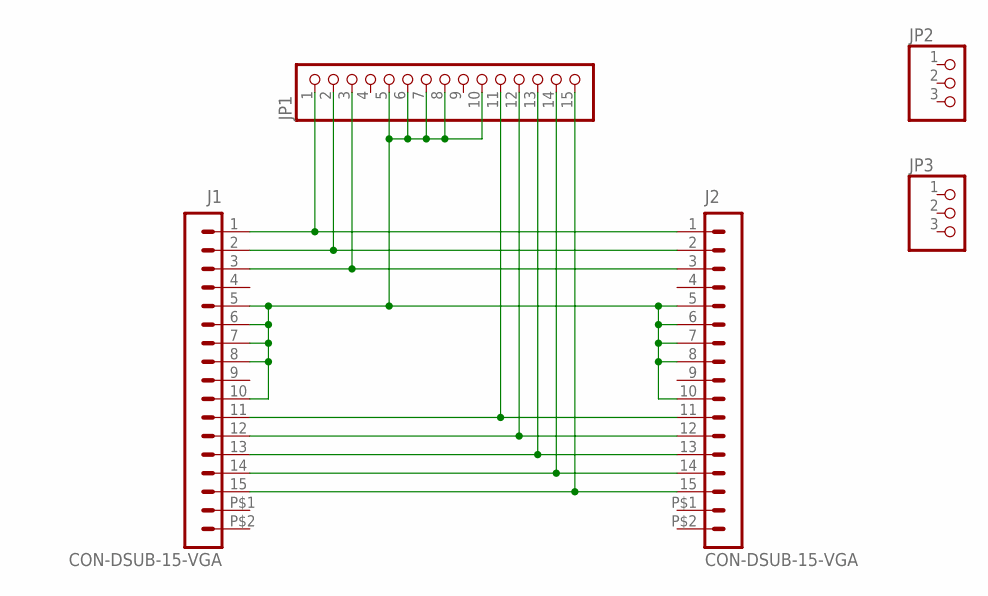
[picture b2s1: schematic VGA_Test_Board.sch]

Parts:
J1, J2: CON-DSUB-15-VGA; 181-015-212-171
JP1: PINHD-1X15; 1X15
JP2, JP3: PINHD-1X3; 1X03

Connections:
GND: J1.5, J1.6, J1.7, J1.8, J1.10, J2.5, J2.6, J2.7, J2.8, J2.10, JP1.5, JP1.6, JP1.7, JP1.8, JP1.10
unnamed: J1.1, J2.1, JP1.1
unnamed: J1.2, J2.2, JP1.2
unnamed: J1.3, J2.3, JP1.3
unnamed: J1.11, J2.11, JP1.11
unnamed: J1.12, J2.12, JP1.12
unnamed: J1.13, J2.13, JP1.13
unnamed: J1.14, J2.14, JP1.14
unnamed: J1.15, J2.15, JP1.15

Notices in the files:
parts and their libraries:
m-pad-2.1: License : GNU General Public License version 2 (see bottom)
